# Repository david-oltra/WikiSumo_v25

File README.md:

<H1>WikiSumo</H1>
<H2>Robot de competicion para la OSHWDEM 2025</H2>

<H2>Hardware</H2>

- ESP32-C3-Supermini
- Sensores TOF VL53L0X
- Sensores IR QRE1113
- Motores JGB37-3530 de 12V (76rpm)
- Driver motor DRV8871

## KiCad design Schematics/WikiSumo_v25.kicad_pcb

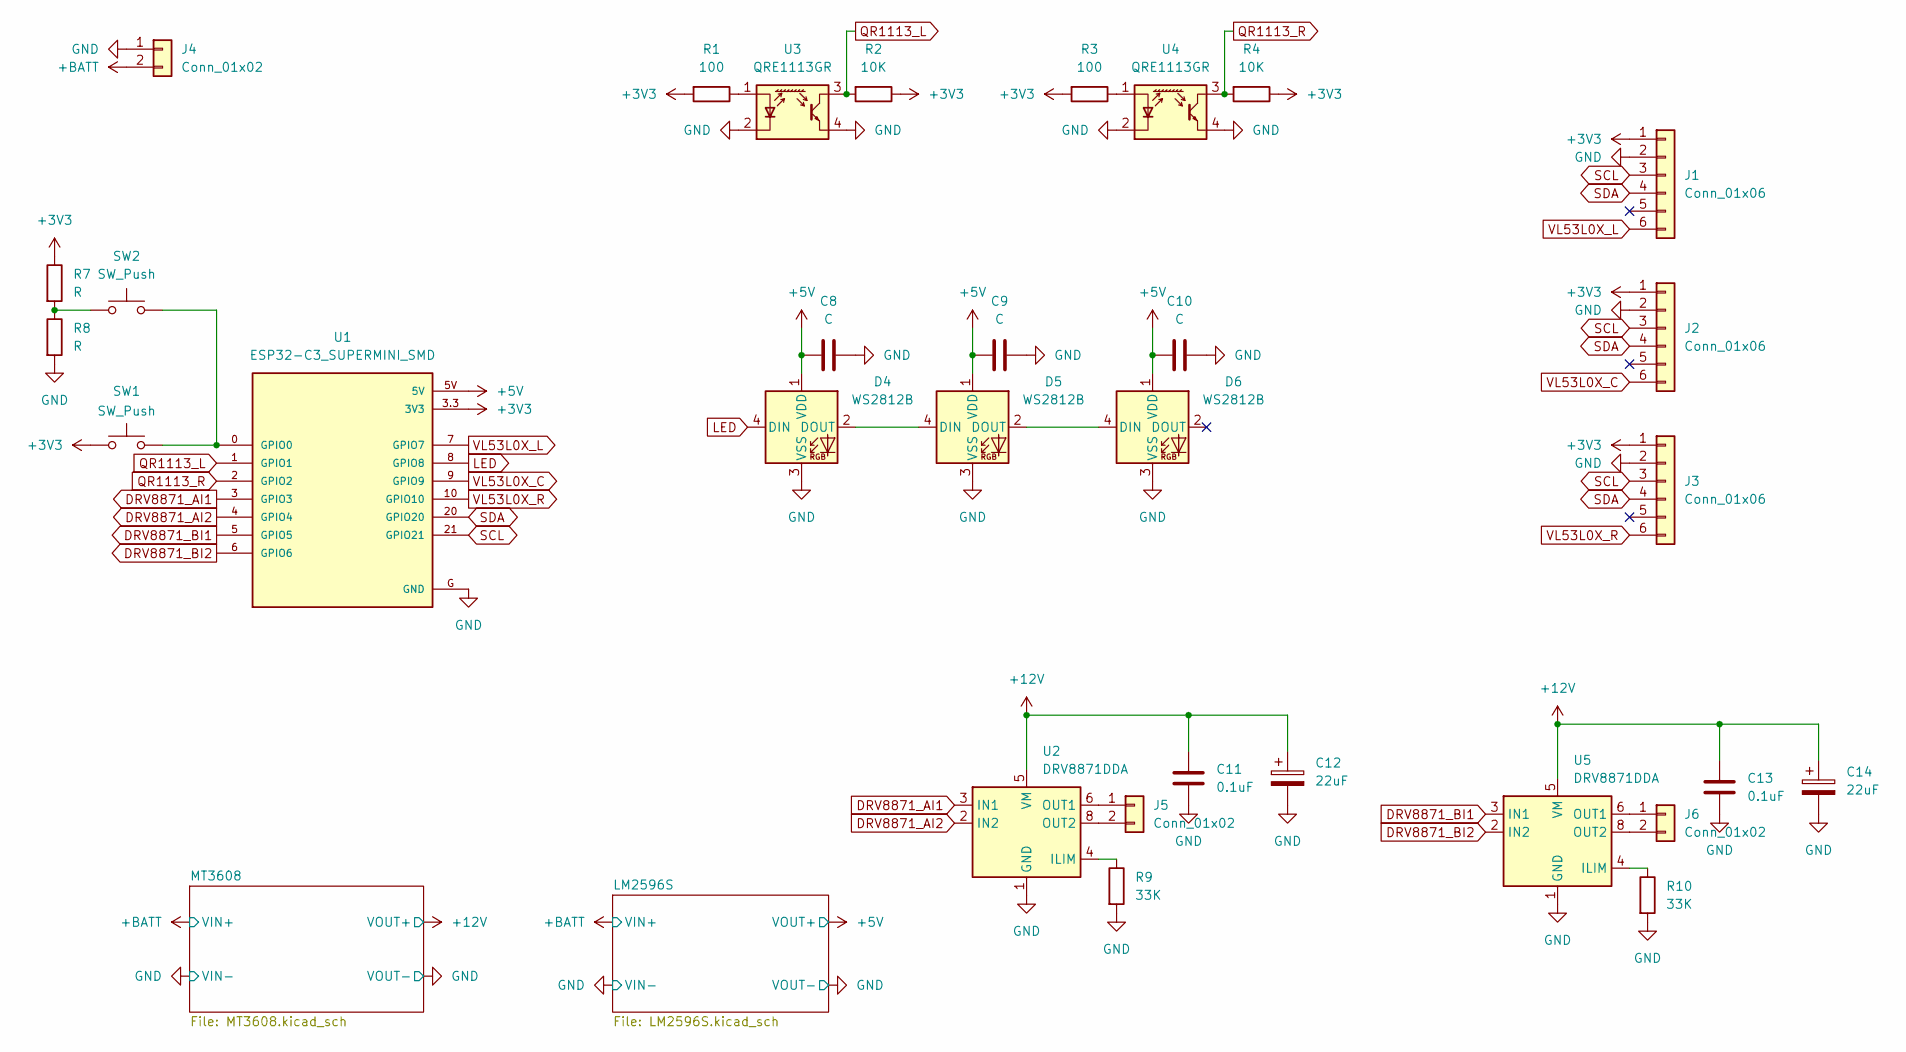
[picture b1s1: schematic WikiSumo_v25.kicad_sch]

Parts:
C8, C9, C10: C; C_0805_2012Metric_Pad1.18x1.45mm_HandSolder
C11, C13: 0.1uF; C_0805_2012Metric_Pad1.18x1.45mm_HandSolder
C12, C14: 22uF; CP_Elec_8x10.5
D4, D5, D6: WS2812B; LED_WS2812B_PLCC4_5.0x5.0mm_P3.2mm
J1, J2, J3: Conn_01x06; PinHeader_1x06_P2.54mm_Vertical
J4, J5, J6: Conn_01x02; JST_PH_B2B-PH-K_1x02_P2.00mm_Vertical
R1, R3: 100; R_0805_2012Metric_Pad1.20x1.40mm_HandSolder
R2, R4: 10K; R_0805_2012Metric_Pad1.20x1.40mm_HandSolder
R7, R8: R; R_0805_2012Metric_Pad1.20x1.40mm_HandSolder
R9, R10: 33K; R_0805_2012Metric_Pad1.20x1.40mm_HandSolder
SW1, SW2: SW_Push; SW_SPST_PTS647_Sx50
U1: ESP32-C3_SUPERMINI_SMD; MODULE_ESP32-C3_SUPERMINI
U2, U5: DRV8871DDA; Texas_HTSOP-8-1EP_3.9x4.9mm_P1.27mm_EP2.95x4.9mm_Mask2.4x3.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
U3, U4: QRE1113GR; OnSemi_CASE100CY

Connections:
+3V3: J1.1, J2.1, J3.1, R1.2, R2.1, R3.2, R4.1, R7.1, SW1.1, U1.3.3 (3V3)
+5V: C8.1, C9.1, C10.1, D4.1 (VDD), D5.1 (VDD), D6.1 (VDD), U1.5V; also elsewhere on the board
+12V: C11.1, C12.1, C13.1, C14.1, U2.5 (VM), U5.5 (VM); also elsewhere on the board
+BATT: J4.2; also elsewhere on the board
DRV8871_AI1: U1.3 (GPIO3), U2.3 (IN1)
DRV8871_AI2: U1.4 (GPIO4), U2.2 (IN2)
DRV8871_BI1: U1.5 (GPIO5), U5.3 (IN1)
DRV8871_BI2: U1.6 (GPIO6), U5.2 (IN2)
GND: C8.2, C9.2, C10.2, C11.2, C12.2, C13.2, C14.2, D4.3 (VSS), D5.3 (VSS), D6.3 (VSS), J1.2, J2.2, J3.2, J4.1, R8.2, R9.2, R10.2, U1.G (GND), U2.1 (GND), U2.7 (GND), U2.9 (GND), U3.2 (K), U3.4, U4.2 (K), U4.4, U5.1 (GND), U5.7 (GND), U5.9 (GND); also elsewhere on the board
LED: D4.4 (DIN), U1.8 (GPIO8)
unnamed: D4.2 (DOUT), D5.4 (DIN)
unnamed: D5.2 (DOUT), D6.4 (DIN)
unnamed: J5.1, U2.6 (OUT1)
unnamed: J5.2, U2.8 (OUT2)
unnamed: J6.1, U5.6 (OUT1)
unnamed: J6.2, U5.8 (OUT2)
unnamed: R7.2, R8.1, SW2.1
unnamed: SW1.2, SW2.2, U1.0 (GPIO0)
unnamed: R9.1, U2.4 (ILIM)
unnamed: R1.1, U3.1 (A)
unnamed: R3.1, U4.1 (A)
unnamed: R10.1, U5.4 (ILIM)
QR1113_L: R2.2, U1.1 (GPIO1), U3.3
QR1113_R: R4.2, U1.2 (GPIO2), U4.3
SCL: J1.3, J2.3, J3.3, U1.21 (GPIO21)
SDA: J1.4, J2.4, J3.4, U1.20 (GPIO20)
VL53L0X_C: J2.6, U1.9 (GPIO9)
VL53L0X_L: J1.6, U1.7 (GPIO7)
VL53L0X_R: J3.6, U1.10 (GPIO10)

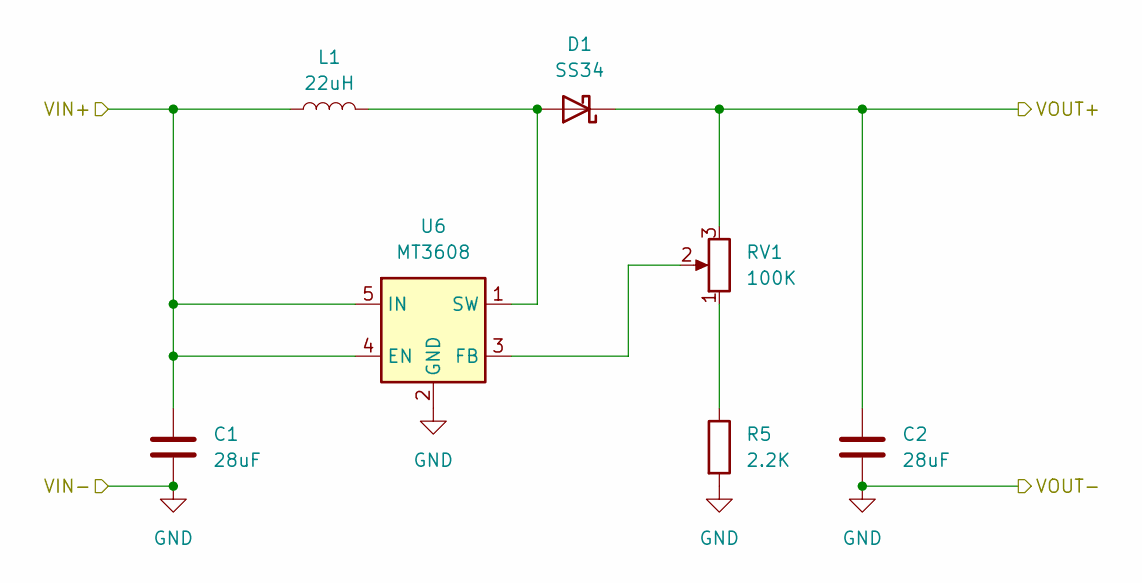
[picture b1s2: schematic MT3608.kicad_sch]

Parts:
C1, C2: 28uF; C_1206_3216Metric_Pad1.33x1.80mm_HandSolder
D1: SS34; D_SMA
L1: 22uH; L_TDK_SLF10165
R5: 2.2K; R_0805_2012Metric_Pad1.20x1.40mm_HandSolder
RV1: 100K; Potentiometer_Bourns_3296P_Horizontal
U6: MT3608; SOT-23-6

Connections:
+12V: C2.1, D1.1 (K), RV1.3; also elsewhere on the board
+BATT: C1.1, L1.1, U6.4 (EN), U6.5 (IN); also elsewhere on the board
GND: C1.2, C2.2, R5.2, U6.2 (GND); also elsewhere on the board
unnamed: D1.2 (A), L1.2, U6.1 (SW)
unnamed: R5.1, RV1.1
unnamed: RV1.2, U6.3 (FB)

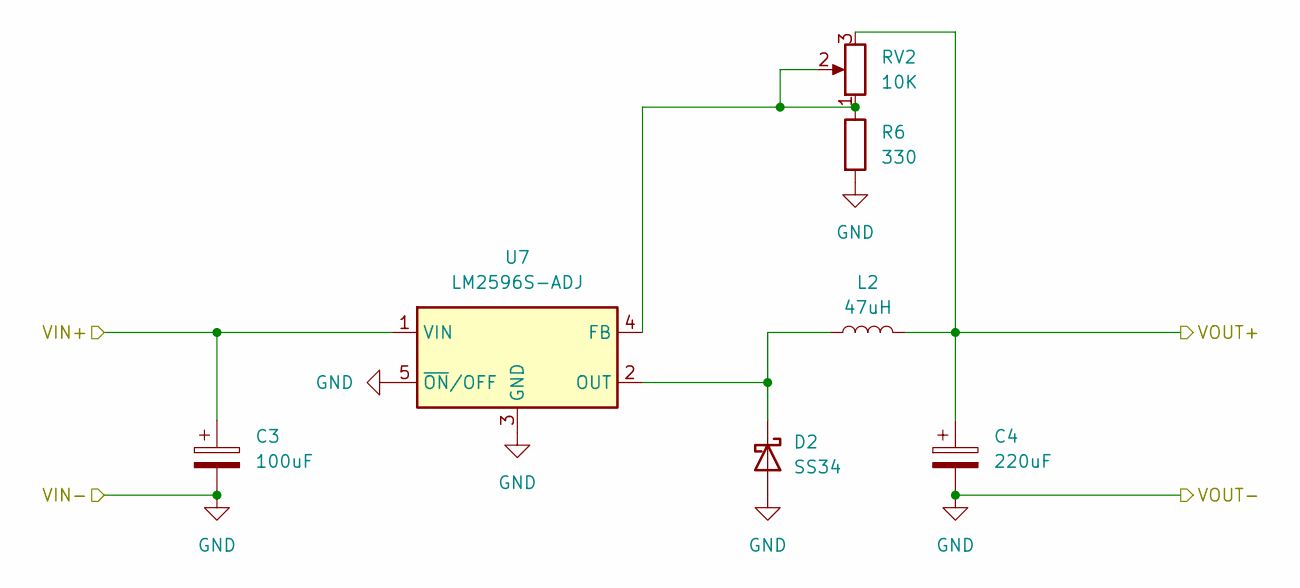
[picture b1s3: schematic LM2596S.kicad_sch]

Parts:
C3: 100uF; CP_Elec_8x10.5
C4: 220uF; CP_Elec_8x10.5
D2: SS34; D_SMA
L2: 47uH; L_12x12mm_H8mm
R6: 330; R_0805_2012Metric_Pad1.20x1.40mm_HandSolder
RV2: 10K; Potentiometer_Bourns_3296W_Vertical
U7: LM2596S-ADJ; TO-263-5_TabPin3

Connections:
+5V: C4.1, L2.2, RV2.3; also elsewhere on the board
+BATT: C3.1, U7.1 (VIN); also elsewhere on the board
GND: C3.2, C4.2, D2.2 (A), R6.2, U7.3 (GND), U7.5 (~ON/OFF); also elsewhere on the board
unnamed: D2.1 (K), L2.1, U7.2 (OUT)
unnamed: R6.1, RV2.1, RV2.2, U7.4 (FB)

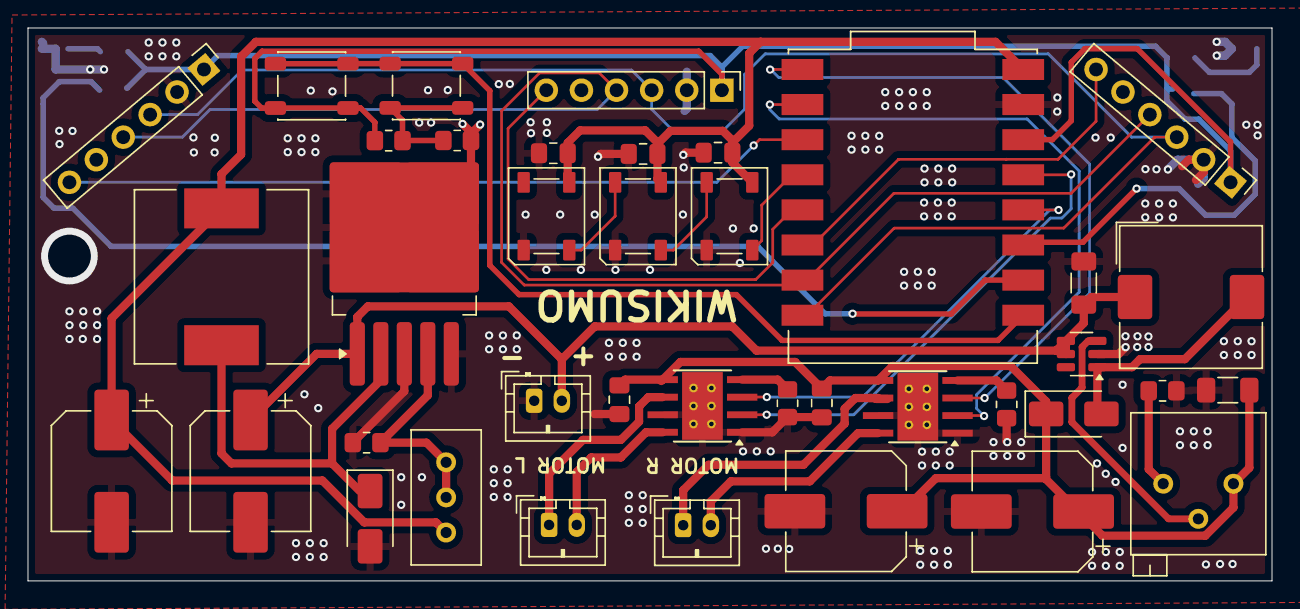
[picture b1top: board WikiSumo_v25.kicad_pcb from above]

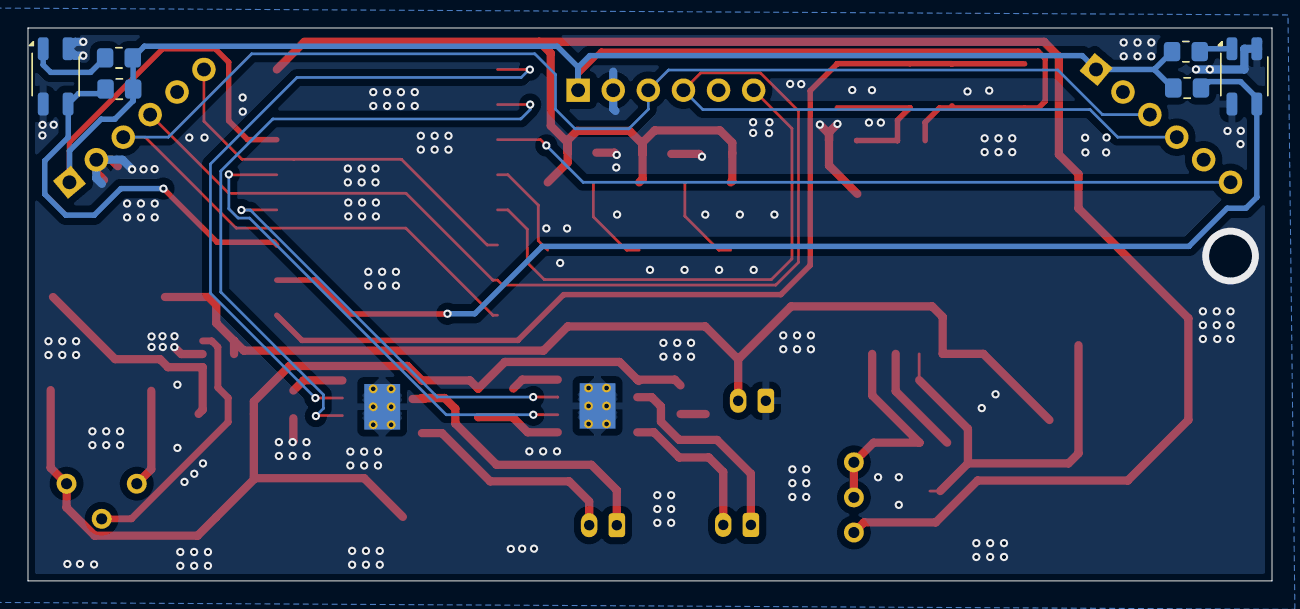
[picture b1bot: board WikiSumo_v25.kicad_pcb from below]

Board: 2 copper layers, 90.0 x 40.0 mm, 45 parts (6 on the bottom side), 34 nets.

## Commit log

2025-09-22 add stl
2025-10-01 Debug
